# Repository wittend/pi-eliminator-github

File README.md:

# pi-eliminator

Hardware design for the Pi-Eliminator, a component of the Personal Space Weather Station (PSWS) project.
Official documentation for this project can be found at [pi-eliminator](https://pi-eliminator.readthedocs.io/).
## Overview
 
The Pi-Eliminator is designed to interface with SDR hardware, specifically related to the ClementineSDR and projects involving the LTC2208 ADC. It appears to serve as an interface or replacement for Raspberry Pi-based setups in these systems, featuring standard 2x20 pin headers.

## Project Structure

- `pi-eliminator.kicad_sch`: Schematic file.
- `pi-eliminator.kicad_pcb`: PCB layout file.
- `production/`: Manufacturing files (BOM, Gerbers, etc.).
- `Local Resources/`: Datasheets, design notes, and reference bitmaps.
- `docs/`: Documentation for ReadTheDocs.

## Documentation

Documentation is prepared for ReadTheDocs and can be found in the `docs/` folder. It covers project requirements, objectives, hardware design, and assembly/setup guides.

## License

This project is licensed under the GNU General Public License v3.0 or later - see the [LICENSE](LICENSE) file for details.

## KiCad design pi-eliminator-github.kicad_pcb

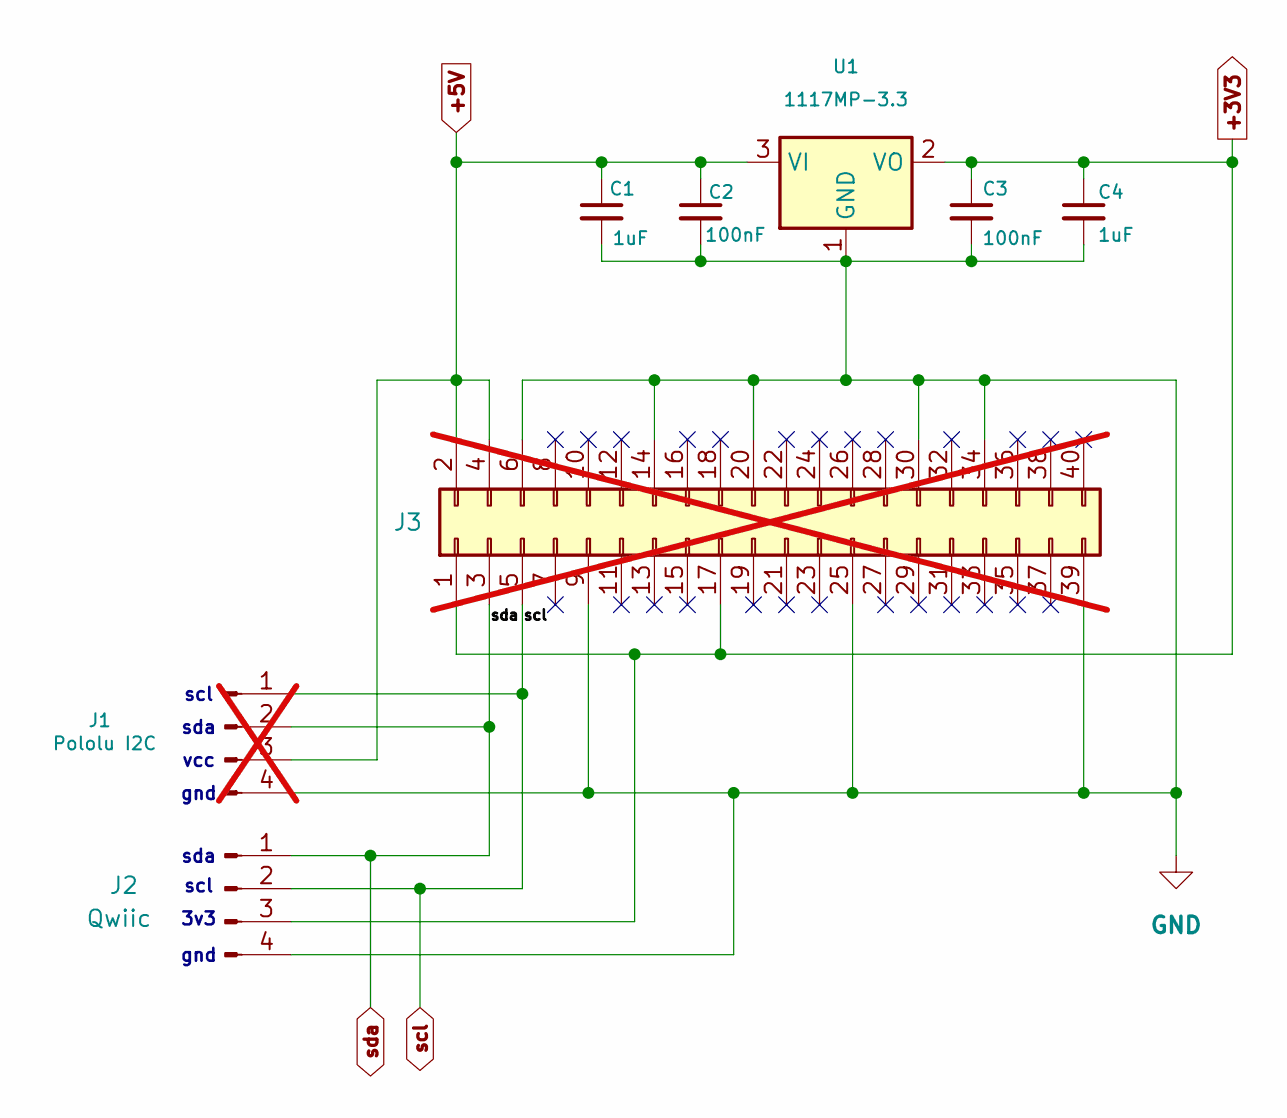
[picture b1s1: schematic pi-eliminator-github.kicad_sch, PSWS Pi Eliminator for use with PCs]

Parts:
C1, C4: 1uF; C_0603_1608Metric
C2, C3: 100nF; C_0603_1608Metric
J1: Pololu I2C; not fitted
J2: Qwiic; JST_SM04B-SRSS-TB_LF__SN_
J3: Conn_02x20_Odd_Even; PinHeader_2x20_P2.54mm_Vertical; not fitted
U1: 1117MP-3.3; SOT-223-3_TabPin2

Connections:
+3V3: C3.1, C4.1, J2.3, J3.1, J3.17, U1.2 (VO)
+5V: C1.1, C2.1, J1.3, J3.2, J3.4, U1.3 (VI)
GND: C1.2, C2.2, C3.2, C4.2, J1.4, J2.4, J2.S1, J2.S2, J3.6, J3.9, J3.14, J3.20, J3.25, J3.30, J3.34, J3.39, U1.1 (GND)
scl: J1.1, J2.2, J3.5
sda: J1.2, J2.1, J3.3

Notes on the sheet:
sda
gnd
vcc
3v3
scl

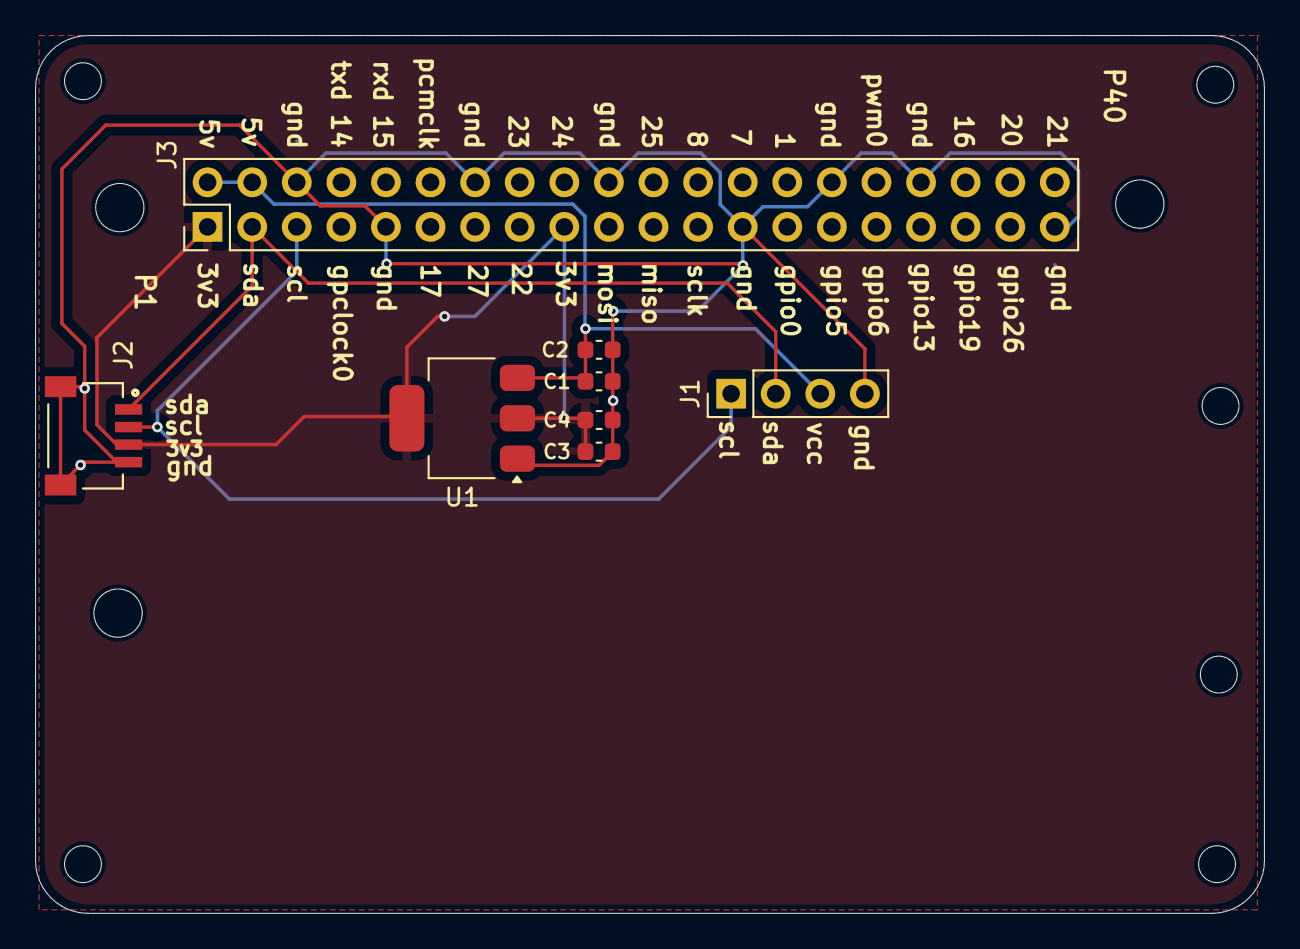
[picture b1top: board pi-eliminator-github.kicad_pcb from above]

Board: 2 copper layers, 70.0 x 50.0 mm, 8 parts (0 on the bottom side), 5 nets.

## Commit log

2026-05-24 Initial commit.
2026-05-25 Revert "Initial commit"
    This reverts commit 4ec67e2a687ef3fee5d076bc886b8d4a376d9653.
    # Conflicts:
    # .gitignore
    # Local Resources/JST/JST_SM04B-SRSS-TB_LF__SN_.kicad_mod
    # Local Resources/bitmaps/pi-eliminator-github.jpg
    # Local Resources/bitmaps/pi-eliminator-github.png
2026-05-25 add .readthedocs.yaml
2026-05-25 Try to fix errors in the readthedocs pipeline.
2026-05-26 Adding bitmaps for the pi-eliminator project.
2026-05-26 Expanding the documentation and adding images.
2026-05-26 Adding to requiremwnts to shape the output of the resulting project and documentation.
